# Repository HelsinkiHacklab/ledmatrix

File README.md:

ledmatrix
=========

Control software for large RGB LED matrix, currently imageconverter directory
contains the interesting stuff.

beagle_spi_documentation.md is probably worth a look as well.

max33xxE_somethign -files contain library and a breakout board for this voltage translator, needed to make the beagleboard talk with 5V logic.

Pics: 

  - <http://assembly.galleria.fi/kuvat/Assembly+Summer+2014/Aleksi+Kinnunen/_V7Q6632.jpg>

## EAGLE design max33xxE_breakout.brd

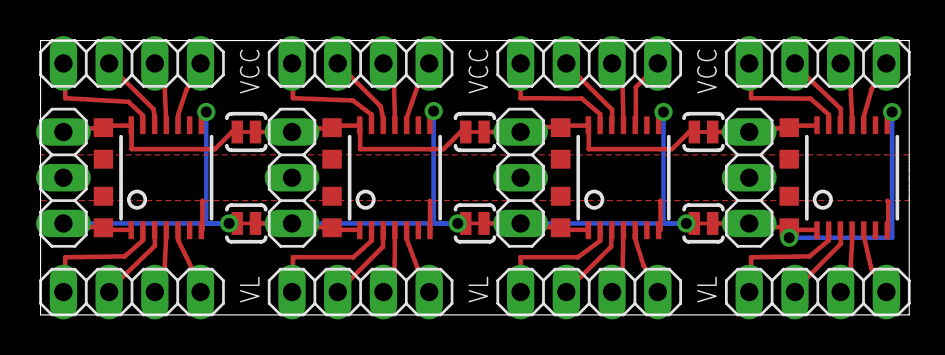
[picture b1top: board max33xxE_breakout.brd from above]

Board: 2 copper layers, 48.3 x 15.2 mm, 30 parts (0 on the bottom side), 41 nets.

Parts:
C1, C2, C3, C4, C5, C6, C7, C8: C0603K
IOVCC_SHIFT1, IOVCC_SHIFT2, IOVCC_SHIFT3, IOVCC_SHIFT4: 1X04
IOVL_SHIFT1, IOVL_SHIFT2, IOVL_SHIFT3, IOVL_SHIFT4: 1X04
PWR_SHIFT1, PWR_SHIFT2, PWR_SHIFT3, PWR_SHIFT4: 1X03
SHIFT1, SHIFT2, SHIFT3, SHIFT4: MAX3378E; TSSOP14
SJ1, SJ2, SJ3, SJ4, SJ5, SJ6: SOLDERJUMPERTRACE; SJ_2S-TRACE

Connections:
GND: C1.2, C2.2, C3.2, C4.2, C5.2, C6.2, C7.2, C8.2, PWR_SHIFT1.2, PWR_SHIFT2.2, PWR_SHIFT3.2, PWR_SHIFT4.2, SHIFT1.7, SHIFT2.7, SHIFT3.7, SHIFT4.7
IOVCC1_SHIFT1: IOVCC_SHIFT1.1, SHIFT1.13
IOVCC1_SHIFT2: IOVCC_SHIFT2.1, SHIFT2.13
IOVCC1_SHIFT3: IOVCC_SHIFT3.1, SHIFT3.13
IOVCC1_SHIFT4: IOVCC_SHIFT4.1, SHIFT4.13
IOVCC2_SHIFT1: IOVCC_SHIFT1.2, SHIFT1.12
IOVCC2_SHIFT2: IOVCC_SHIFT2.2, SHIFT2.12
IOVCC2_SHIFT3: IOVCC_SHIFT3.2, SHIFT3.12
IOVCC2_SHIFT4: IOVCC_SHIFT4.2, SHIFT4.12
IOVCC3_SHIFT1: IOVCC_SHIFT1.3, SHIFT1.11
IOVCC3_SHIFT2: IOVCC_SHIFT2.3, SHIFT2.11
IOVCC3_SHIFT3: IOVCC_SHIFT3.3, SHIFT3.11
IOVCC3_SHIFT4: IOVCC_SHIFT4.3, SHIFT4.11
IOVCC4_SHIFT1: IOVCC_SHIFT1.4, SHIFT1.10
IOVCC4_SHIFT2: IOVCC_SHIFT2.4, SHIFT2.10
IOVCC4_SHIFT3: IOVCC_SHIFT3.4, SHIFT3.10
IOVCC4_SHIFT4: IOVCC_SHIFT4.4, SHIFT4.10
IOVL1_SHIFT1: IOVL_SHIFT1.1, SHIFT1.2
IOVL1_SHIFT2: IOVL_SHIFT2.1, SHIFT2.2
IOVL1_SHIFT3: IOVL_SHIFT3.1, SHIFT3.2
IOVL1_SHIFT4: IOVL_SHIFT4.1, SHIFT4.2
IOVL2_SHIFT1: IOVL_SHIFT1.2, SHIFT1.3
IOVL2_SHIFT2: IOVL_SHIFT2.2, SHIFT2.3
IOVL2_SHIFT3: IOVL_SHIFT3.2, SHIFT3.3
IOVL2_SHIFT4: IOVL_SHIFT4.2, SHIFT4.3
IOVL3_SHIFT1: IOVL_SHIFT1.3, SHIFT1.4
IOVL3_SHIFT2: IOVL_SHIFT2.3, SHIFT2.4
IOVL3_SHIFT3: IOVL_SHIFT3.3, SHIFT3.4
IOVL3_SHIFT4: IOVL_SHIFT4.3, SHIFT4.4
IOVL4_SHIFT1: IOVL_SHIFT1.4, SHIFT1.5
IOVL4_SHIFT2: IOVL_SHIFT2.4, SHIFT2.5
IOVL4_SHIFT3: IOVL_SHIFT3.4, SHIFT3.5
IOVL4_SHIFT4: IOVL_SHIFT4.4, SHIFT4.5
VCC_SHIFT1: C2.1, PWR_SHIFT1.1, SJ1.1
VCC_SHIFT2: C4.1, PWR_SHIFT2.1, SHIFT2.14, SJ1.2, SJ5.1
VCC_SHIFT3: C6.1, PWR_SHIFT3.1, SHIFT3.14, SJ4.1, SJ5.2
VCC_SHIFT4: C8.1, PWR_SHIFT4.1, SHIFT4.14, SJ4.2
VL_SHIFT1: C1.1, PWR_SHIFT1.3, SHIFT1.1, SHIFT1.8, SJ6.1
VL_SHIFT2: C3.1, PWR_SHIFT2.3, SHIFT2.1, SHIFT2.8, SJ2.1, SJ6.2
VL_SHIFT3: C5.1, PWR_SHIFT3.3, SHIFT3.1, SHIFT3.8, SJ2.2, SJ3.1
VL_SHIFT4: C7.1, PWR_SHIFT4.3, SHIFT4.1, SHIFT4.8, SJ3.2

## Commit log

2012-11-04 Suovulas Arduino code for driving the beast
2013-10-01 stub
2013-10-01 stubity stub
2013-10-01 document
2013-10-06 workgin on conversion
2013-10-06 this should work, but the row flip looks a bit wrong
2013-10-06 trivial state machine
2013-10-06 this shuould ouput something
2013-10-06 this sorta works, the pattern is still broken but that probably is not a problem with the SPI bridge
2013-10-06 for some reason the row flip does not quite work for all columns
2013-10-06 make less noise
2013-10-06 better name
2013-10-06 it seems we are bitten by pointers, so make a new array for the flipped data
2013-10-06 less debug
2013-10-06 it seems fit does antialias even when there is nothing to be done
2013-10-06 use "constants" instead of magic numbers
2013-10-06 resize on demand
2013-10-06 animation support, though sending the data over the UART is too slow
2013-10-06 spec says it is 1/100s but 1/1000 seems a lot better
2013-10-06 a TODO
2013-10-07 according to stackoverflow this is the correct way to yield (as opposed to some epsilon value)
2013-10-12 started working on version that uses SPIlib
2013-10-12 this ought to work
2013-10-12 use correct name
2013-10-12 apparently the buffer is given as string
2013-10-12 wedo not need the sleep to see responses from the arduino here
2013-10-12 just a note
2013-10-13 started with an example
2013-10-13 basically all of this is still untested...
2013-10-13 copy the ZMQ examples build script
2013-10-13 this seems to be requires by the zmq examples build script too
2013-10-13 adjustments
2013-10-13 trying to figure this out
2013-10-13 ZMQ version notes
2013-10-13 free the malloced data
2013-10-13 the macro will not help us now
2013-10-13 memcpy is in string.h, go figure...
2013-10-13 handle failed malloc
2013-10-13 use the same helper
2013-10-13 lets see if this helps to the implicit declaration issue I am seeing
2013-10-13 gah, overlapping names, this should be better
2013-10-13 fix search/replace typos, adjust the default spidev device
2013-10-13 better error handling
2013-10-13 oops..
2013-10-13 prettying
2013-10-13 nonblocking messages, better error reporting
2013-10-13 check for the interrupt FIRST
2013-10-13 copy as base
2013-10-13 make +x
2013-10-13 added README
2013-10-13 readme
2013-10-13 clarify
2013-10-13 trivial application to test the bridge
2013-10-13 completely untested
2013-10-13 fix copy-paste error
2013-10-13 and connect, not bind...
2013-10-13 list does not implement buffer interface so join to string
2013-10-13 we are client now, connect...
2013-10-13 fixed and debugs
2013-10-13 missing newlines
2013-10-13 test increasing size of payload
2013-10-13 string arguments must be copied, especially if there are multiple
2013-10-13 for some reason specifying the -D works but -S causes segfault
2013-10-13 ah my opt parser format was wrong
2013-10-13 typo fixes
2013-10-13 allow specifying start position too
2013-10-13 note about library I had to install
2013-10-13 keep track of this document, I guess I will put it up to gist as well
2013-10-13 I need to go to sleep now
2013-10-14 document setting up the bridge (and testing the kernel device with a simpler setup before that)
2013-10-14 this is now documented
2013-10-14 explain the 160 byte limit
2013-10-14 typos and clarifications
2013-10-14 maybe now it will be a blockquote
2013-10-14 try to fix spacing issues
2013-10-14 this makes the blockquote, there is still extra p-tag but that can stay
2013-10-14 note that there is an official cable adapter as well
2013-10-14 minor fixes
2013-10-14 no need to start from 1 here
2013-10-14 it seems kernel 3.8 solves my problem
2013-10-14 missed ./
2013-10-14 typo fix
2013-10-14 add quiet and verbose modes
2013-10-14 confifgure yielding
2013-10-14 exit after printing usage
2013-10-15 Make this important note bold
2013-10-15 typo, language
2013-10-15 some more test images
2013-10-17 notes about usb wifi adapters
2013-10-17 this bit me once with a Raspberry pi
2013-10-17 more test images
2013-10-19 this should now work without numpy
2013-11-04 mix and match example code
2013-11-04 beat detection seems to work
2013-11-04 cleaner example, we do not yet use any of these
2013-11-04 QT PIL image test from http://skilldrick.co.uk/2010/03/pyqt-pil-and-windows/
2013-11-04 this works
2013-11-04 explicitly import from PIL instead of trusting some magic to figure it out
2013-11-04 visualize beats
2013-11-04 comments
2013-11-04 experimenting with fft code
2013-11-04 trying to figure this example code out and adjust to my matrix
2013-11-04 refactoring in preparation for drawing the level bars
2013-11-04 invert the visualization
2013-11-04 tried to optimize a bit, it seems the main problem is the naive draw loop
2013-11-05 scaling works better
2013-11-05 adjust the scaliong
2013-11-05 this works relatively well
2013-11-05 this is starting to look like something
2013-11-05 it almost works
2013-11-05 int16 not uint, but still I get PCM underruns
2013-11-05 adjusting the buffersize does not really help
2013-11-05 cleanup, and remember to use floats
2013-11-06 it seems trying to use direct pyaudio output like this was a mistake, just write the chirp to a file...
2013-11-06 move the audio init
2013-11-06 some comments
2013-11-06 going towards more async approach
2013-11-07 we were falling behind, process the chunks more often
2013-11-07 wider sweep
2013-11-07 well, that is the theory anyway, does not seem to work work me (neither in mode 0x004)
2013-11-09 caveat emptor
2013-11-10 uaargh, my problems with gpio were caused by the fact that I was using ssh and connecting to the wrong board...
2013-11-10 updated note
2013-11-12 simple helper script for dringin the GPIO outputs from shell
2013-11-12 send the image data to the matrix if zmq connect string is defined, but this falls a lot behind on the updates for some reason
2013-11-12 even when limiting the update freq we still fall behind
2013-11-12 analyze_audio does not complain about falling behind and the matrix follows the QT image just about as perfectly as I can see, but both have signigicant lag vs the audio
2013-11-12 5 chunks should be 100ms of audio, but still it does not complain about falling behind even though the lag is clear
2013-11-12 interesting that this worked before, still having lag though, maybe I should make it properly threaded
2014-01-15 sleep(0) is a valid yield, but use the sync mode and goto instead
2014-01-15 flags are required even when unused
2014-01-15 forgot goto *must* stay in scope, so cannot jump like this from the sync recv interrupt
2014-01-15 checking for EINTR and using blocking mode seems to be most efficient for my use case
2014-01-15 put the zmq updat to separate thread but still the FFT lags like hell when zmq output is used
2014-07-09 copied tssop-14 package from microbuilder.eu library
2014-07-09 first device
2014-07-09 they have same symbol and connections, just the speed is different
2014-07-09 soon there will ve more of these blocks here
2014-07-09 ignore eagle temp files
2014-07-09 rename the power segments too
2014-07-09 apparently the automatic net rename when copying does not quite work if the nets are not actually drawn all the way through
2014-07-09 quick first placement
2014-07-09 remove the cluttering names
2014-07-09 verified that pinheaders align cleanly on 100mil grid
2014-07-09 size down the board
2014-07-09 bypass caps
2014-07-09 join the separate VCC and VL segments with solderpads
2014-07-09 use Seeeds DRU
2014-07-09 add a groundplane
2014-07-09 autorouted and minor adjustments to the result
2014-07-09 I wonder why the autorouter did not route these, maybe some keepout somewhere ?
2014-07-09 route the VCC solder jumpers
2014-07-09 add vias to route the VL solder jumpers from bottom
2014-07-09 handle some DRC errors
2014-07-09 mark the VCC and VL sides
2014-07-09 isolate the ground plane more just in case I try to make etch this as single layer board at home
2014-07-09 notes about the breakout
2014-07-09 forgot that the -THREESTATE *must* be pulled to VCC/VL
2014-07-09 daym, -threestate must be pulled VL not VCC, good that I verified this...
2014-07-09 route the VL pull-ups via bottom
2014-07-09 saner grid
2014-07-10 so you do not need Eagle to view these
2014-07-10 this ought to be etchable at home, the mask is already "upside down", you will need to solder separate jumper wires for the bottom side connections
2014-07-29 3.8 was marked as inactive in upstream
2014-07-31 loop gifs
2014-07-31 start writing async server
2014-08-01 karolains animation
2014-08-03 photo of the matrix running karolains nyan-cat animation
2014-08-09 untested zmq router socket that takes a flattened list of byter, remakes it into array, does the requires row-flips and passes it on
2014-08-09 correct the number of args, send reply to client
2014-08-09 make executable
2015-08-15 Vaihtuvat animaatiot ja cccamp15-giffi
2016-03-30 allow any number of space before main arguments
2016-04-01 allow any amount of space before main function
2016-04-01 Add timing info

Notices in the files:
parts and their libraries:
SparkFun-Passives: Licensing: CC v3.0 Share-Alike You are welcome to use this library for commercial purposes.
